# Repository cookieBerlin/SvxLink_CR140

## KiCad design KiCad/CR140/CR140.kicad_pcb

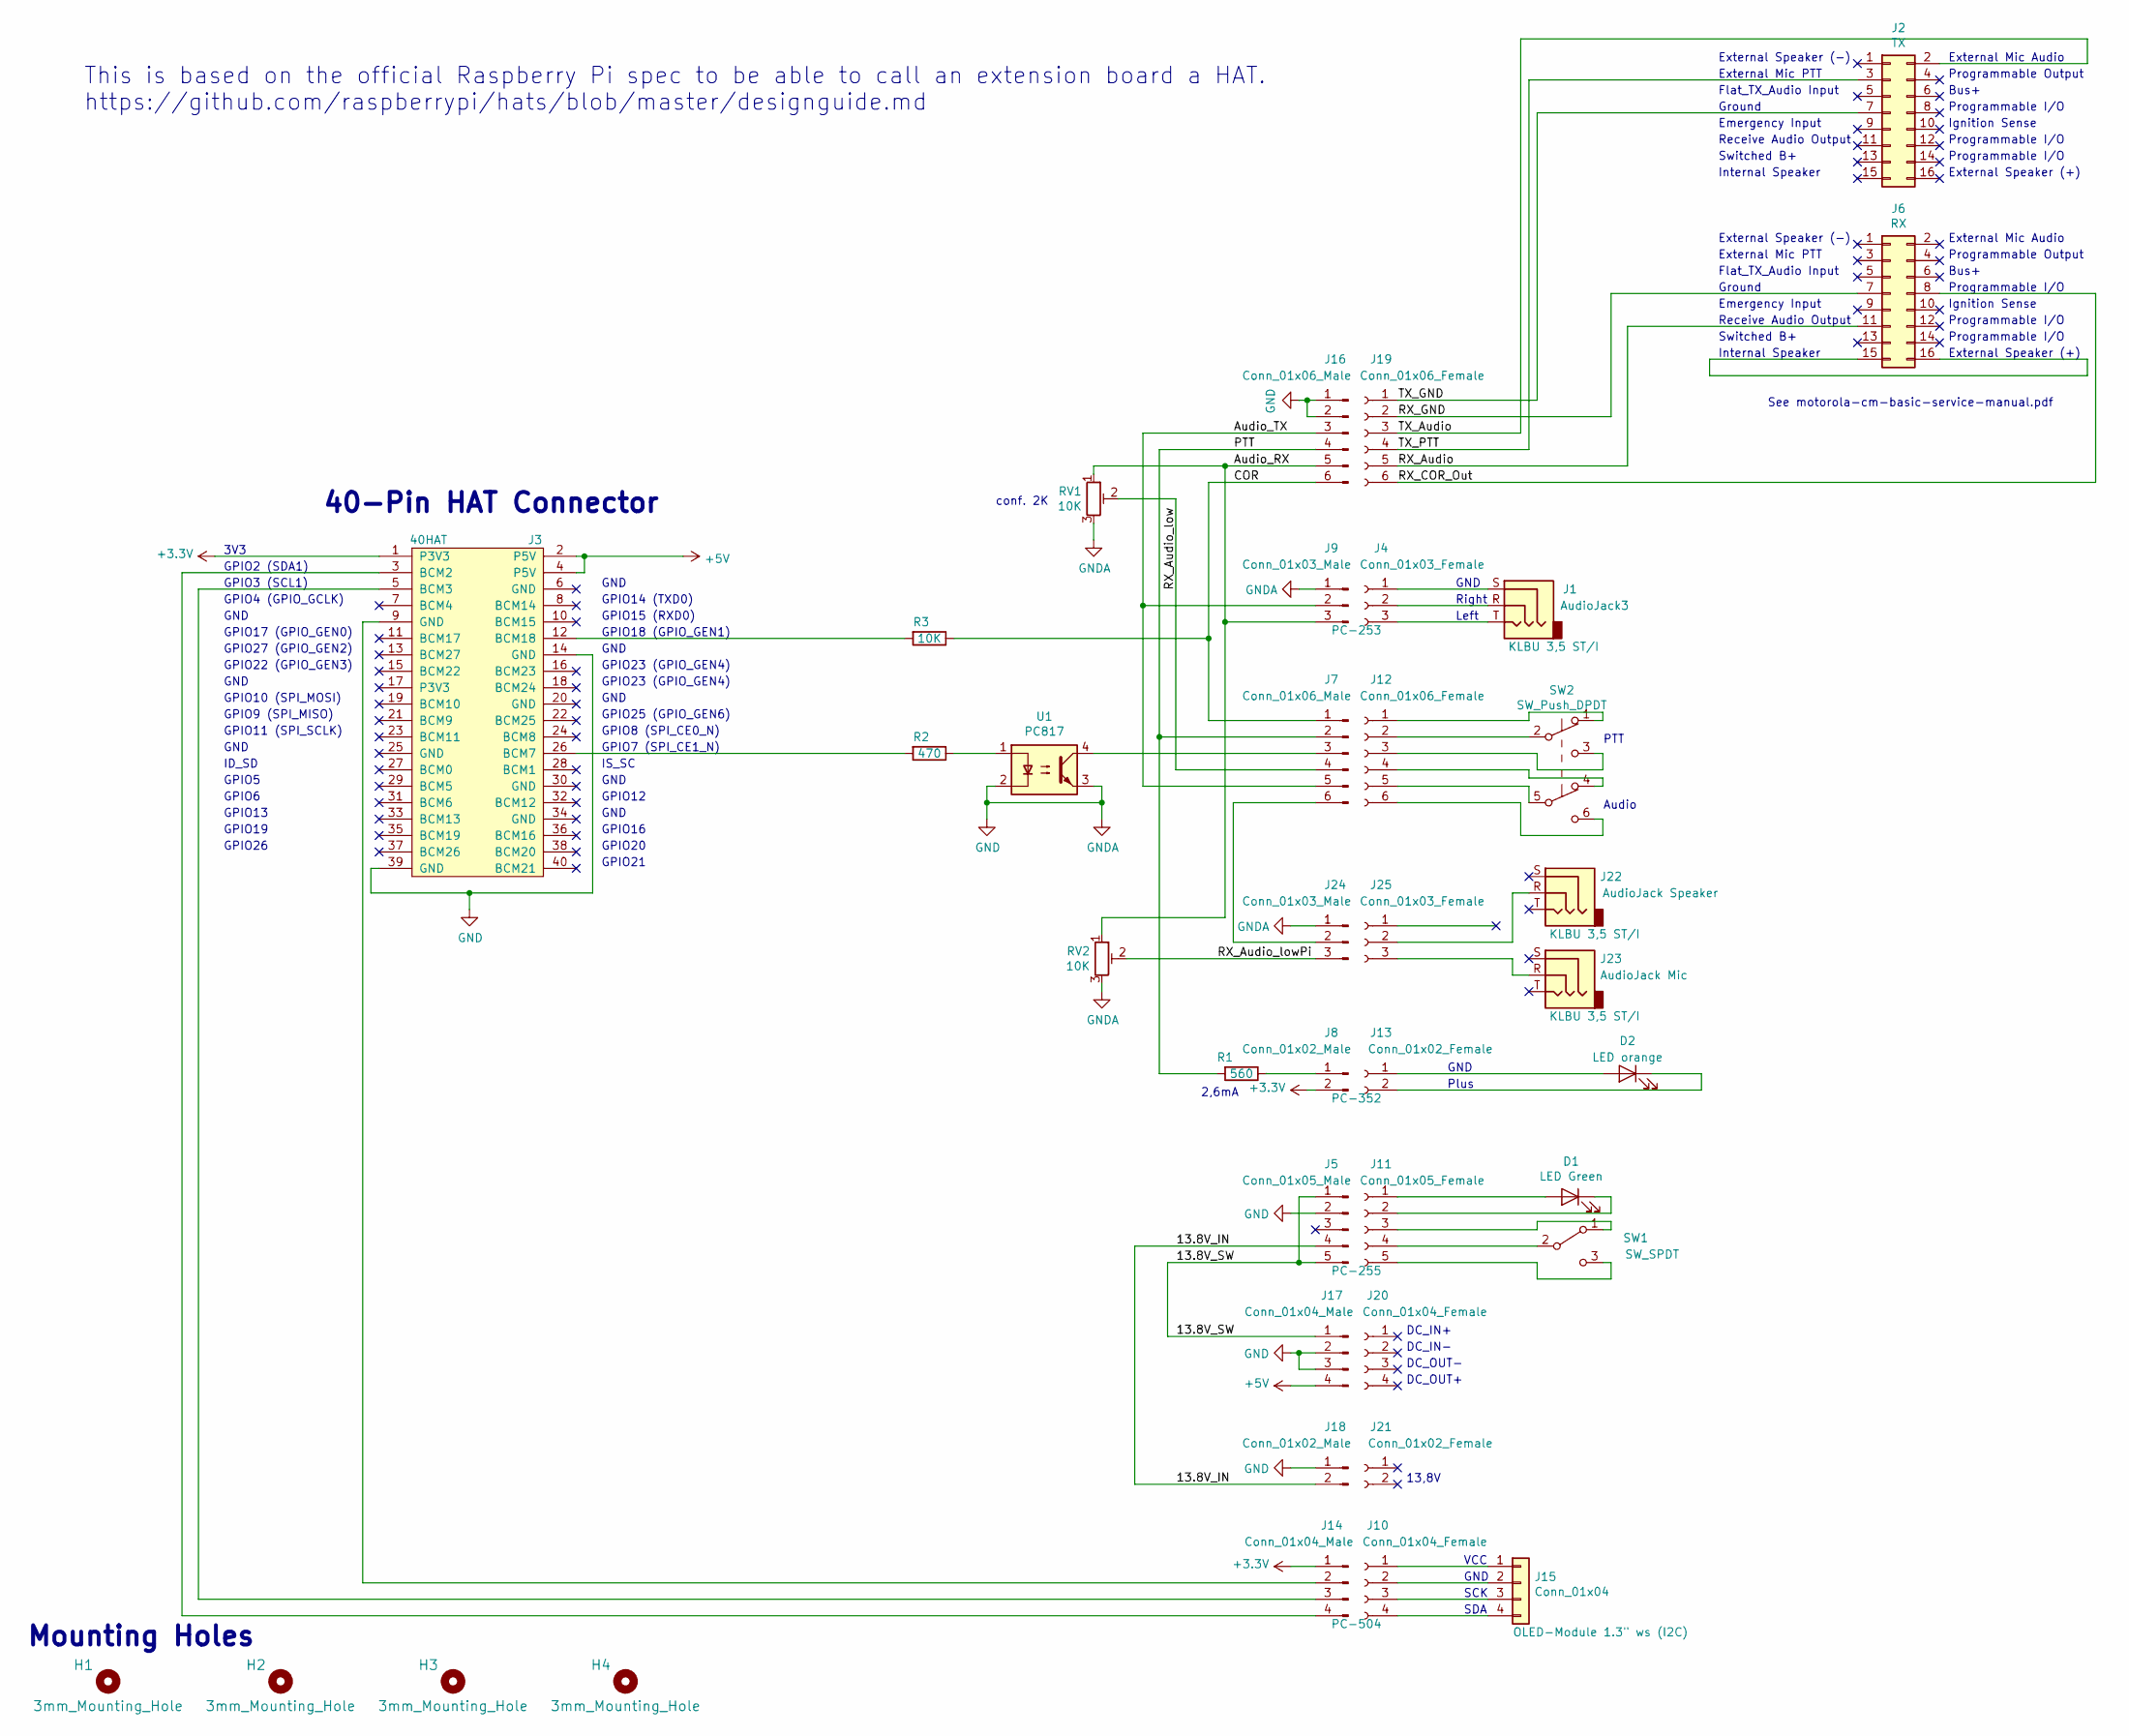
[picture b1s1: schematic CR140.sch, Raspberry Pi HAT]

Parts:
D1: LED Green; LED_D3.0mm
D2: LED orange; LED_D3.0mm
H1, H2, H3, H4: 3mm_Mounting_Hole; NPTH_3mm_ID
J1: AudioJack3; Jack_3.5mm_CUI_SJ1-3533NG_Horizontal
J2: TX; Molex_Nano-Fit_105314-xx16_2x08_P2.50mm_Horizontal
J3: 40HAT; PinSocket_2x20_P2.54mm_Vertical
J4: Conn_01x03_Female; Molex_KK-254_AE-6410-03A_1x03_P2.54mm_Vertical
J5: Conn_01x05_Male; Molex_KK-254_AE-6410-05A_1x05_P2.54mm_Vertical
J6: RX; Molex_Nano-Fit_105314-xx16_2x08_P2.50mm_Horizontal
J7: Conn_01x06_Male; Molex_KK-254_AE-6410-06A_1x06_P2.54mm_Vertical
J8: Conn_01x02_Male; Molex_KK-254_AE-6410-02A_1x02_P2.54mm_Vertical
J9: Conn_01x03_Male; Molex_KK-254_AE-6410-03A_1x03_P2.54mm_Vertical
J10, J20: Conn_01x04_Female; PinHeader_1x04_P2.54mm_Vertical
J11: Conn_01x05_Female; Molex_KK-254_AE-6410-05A_1x05_P2.54mm_Vertical
J12: Conn_01x06_Female; Molex_KK-254_AE-6410-06A_1x06_P2.54mm_Vertical
J13: Conn_01x02_Female; Molex_KK-254_AE-6410-02A_1x02_P2.54mm_Vertical
J14, J17: Conn_01x04_Male; PinHeader_1x04_P2.54mm_Vertical
J15: Conn_01x04; PinHeader_1x04_P2.54mm_Vertical
J16: Conn_01x06_Male; PinHeader_1x06_P2.54mm_Vertical
J18: Conn_01x02_Male; PinHeader_1x02_P2.54mm_Vertical
J19: Conn_01x06_Female; PinHeader_1x06_P2.54mm_Vertical
J21: Conn_01x02_Female; PinHeader_1x02_P2.54mm_Vertical
J22: AudioJack Speaker; Jack_3.5mm_CUI_SJ1-3533NG_Horizontal
J23: AudioJack Mic; Jack_3.5mm_CUI_SJ1-3533NG_Horizontal
J24: Conn_01x03_Male; PinHeader_1x03_P2.54mm_Vertical
J25: Conn_01x03_Female; PinHeader_1x03_P2.54mm_Vertical
R1: 560; R_Axial_DIN0207_L6.3mm_D2.5mm_P15.24mm_Horizontal
R2: 470; R_Axial_DIN0207_L6.3mm_D2.5mm_P7.62mm_Horizontal
R3: 10K; R_Axial_DIN0207_L6.3mm_D2.5mm_P2.54mm_Vertical
RV1: 10K; Potentiometer_Piher_PT-10-V10_Vertical
RV2: 10K; Potentiometer_Piher_PT-6-V_Vertical
SW1: SW_SPDT; SW_NKK_BB15AH
SW2: SW_Push_DPDT; SW_CuK_JS202011CQN_DPDT_Straight
U1: PC817; DIP-4_W7.62mm

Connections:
+3V3: J3.1 (P3V3), J8.2, J14.1
+5V: J3.2 (P5V), J3.4 (P5V), J17.4
/13.8V_IN: J5.4, J18.2
/13.8V_SW: J5.1, J5.5, J17.1
/Audio_RX: J9.3, J16.5, RV1.1, RV2.1
/Audio_TX: J7.5, J9.2, J16.3
/COR: J7.1, J16.6, R3.1
/PTT: J7.2, J16.4, R1.2
/RX_Audio: J6.11, J19.5
/RX_Audio_low: J7.4, RV1.2
/RX_Audio_lowPi: J24.3, RV2.2
/RX_COR_Out: J6.8, J19.6
/RX_GND: J6.7, J19.2
/TX_Audio: J2.2, J19.3
/TX_GND: J2.7, J19.1
/TX_PTT: J2.3, J19.4
GND: J3.14 (GND), J3.39 (GND), J5.2, J9.1, J16.1, J16.2, J17.2, J17.3, J18.1, J24.1, RV1.3, RV2.3, U1.2, U1.3
unnamed: D1.1 (K), J11.2
unnamed: D1.2 (A), J11.1
unnamed: D2.1 (K), J13.2
unnamed: D2.2 (A), J13.1
unnamed: J1.R, J4.2
unnamed: J1.S, J4.1
unnamed: J1.T, J4.3
unnamed: J3.12 (BCM18), R3.2
unnamed: J3.26 (BCM7), R2.2
unnamed: J6.15, J6.16
unnamed: J7.3, U1.4
unnamed: J8.1, R1.1
unnamed: J10.1, J15.1
unnamed: J10.2, J15.2
unnamed: J10.3, J15.3
unnamed: J10.4, J15.4
unnamed: J11.3, SW1.1 (A)
unnamed: J11.4, SW1.2 (B)
unnamed: J11.5, SW1.3 (C)
unnamed: J12.1, SW2.1 (A)
unnamed: J12.2, SW2.2 (B)
unnamed: J12.3, SW2.3 (C)
unnamed: J12.4, SW2.4 (A)
unnamed: J12.5, SW2.5 (B)
unnamed: J12.6, SW2.6 (C)
unnamed: J3.9 (GND), J14.2
unnamed: J3.5 (BCM3), J14.3
unnamed: J3.3 (BCM2), J14.4
unnamed: J22.R, J25.2
unnamed: J23.R, J25.3
unnamed: J7.6, J24.2
unnamed: R2.1, U1.1

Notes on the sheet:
Mounting Holes
This is based on the official Raspberry Pi spec to be able to call an extension board a HAT. https://github.com/raspberrypi/hats/blob/master/designguide.md
VCC
GND
SCK
SDA
Right
Left
Plus
3V3
GPIO2 (SDA1)
GPIO3 (SCL1)
GPIO4 (GPIO_GCLK)
40-Pin HAT Connector
GPIO17 (GPIO_GEN0)
GPIO27 (GPIO_GEN2)
GPIO22 (GPIO_GEN3)
GPIO10 (SPI_MOSI)
GPIO9 (SPI_MISO)
ID_SD
GPIO11 (SPI_SCLK)
GPIO5
GPIO6
GPIO13
GPIO19
GPIO26
GPIO21
GPIO20
GPIO16
GPIO12
GPIO14 (TXD0)
GPIO15 (RXD0)
GPIO18 (GPIO_GEN1)
GPIO23 (GPIO_GEN4)
GPIO25 (GPIO_GEN6)
GPIO8 (SPI_CE0_N)
GPIO7 (SPI_CE1_N)
IS_SC
Ground
Receive Audio Output

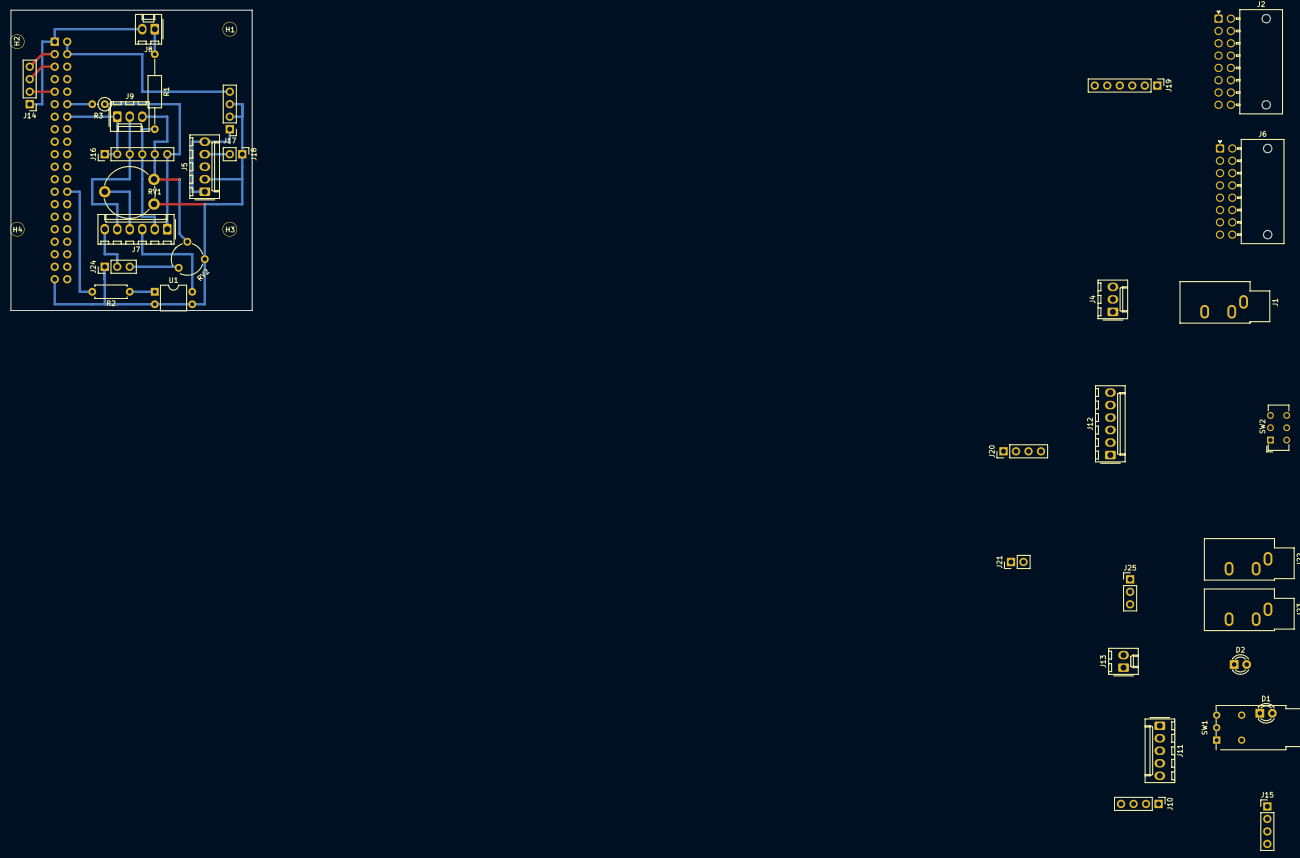
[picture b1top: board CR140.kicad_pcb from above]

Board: 2 copper layers, 49.0 x 61.0 mm, 39 parts (1 on the bottom side), 49 nets.

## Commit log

2019-12-28 add KiCad Files
2019-12-28 add images
